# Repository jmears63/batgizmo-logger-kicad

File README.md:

# BatGizmo Logger

This repo contains hardware design files for the BatGizmo Logger PCB, generated in KiCad, including the schematic, PCB layout, and local symbol/footprint libraries for the logger board.

General information can be found in [this blog post](https://twilighttravels.org/2026/04/04/batgizmo-detector-design/). The [firmware can be found here](https://github.com/jmears63/batgizmo-logger-595).

Open the project files in KiCad to see the most recent PCBs.

## What Is the BatGizmo Logger?

The BatGizmo Logger is an ultrasonic microphone that can be used for bat monitoring in two ways:

- Active monitoring, connected via USB to an Android phone or tablet with the [BatGizmo app](https://play.google.com/store/apps/details?id=uk.org.gimell.batgizmoapp) installed.
- Passive monitoring, powered by 3xAA batteries, capable of recording full-spectrum bat data to WAV files stored on an SD card.

## Board Contents

- STM32U5 series microcontroller
- MEMS microphone front end (Infineon IM73A135) with analog conditioning
- microSD connector for local data logging and configuration
- USB Micro-B connector for power and live audio data in active monitoring mode, plus direct firmware update
- Optional real-time clock powered by a CR1220 battery
- On-board mode switch options and status LEDs

## Getting Started

### Prerequisites

- KiCad 8.x (project files are generated with KiCad 8 format)

### Open the Design

1. Launch KiCad.
2. Open `BatGizmo-logger.kicad_pro`.
3. From the project window, open:
   - schematic editor for `BatGizmo-logger.kicad_sch`
   - PCB editor for `BatGizmo-logger.kicad_pcb`

### Regenerate Outputs

Use KiCad's built-in exporters as needed:

- **Schematic Editor** -> ERC, BOM export
- **PCB Editor** -> DRC, Gerbers, drill files, pick-and-place, fabrication docs

Generated fabrication/output artifacts are intentionally ignored in git (see `.gitignore`), so they can be recreated locally per release.

### Build instructions

Detailed build instructions with photographs can be found in the [WIKI](https://github.com/jmears63/batgizmo-logger-kicad/wiki/Building-BatGizmo)

## License

This project is licensed under the **CERN Open Hardware License v2 - Permissive (CERN-OHL-P v2)**.

See `LICENSE.md` for the full text.

Copyright (c) 2024-2026 John Mears.

## Schematic

Open the project files in KiCad to see the most recent schematic.

## Detailed Design Notes
### Capacitors
Decoupling capacitors are provided throughout in accordance with manufacturers' recommendations.

Be aware that surface mount ceramic capacitors generally use high dielectric constant dielectrics to achieve their small size. Unfortunately, the materials used are often piezo electric, meaning that such capacitors act as audio transducers: they can generate sound and act as microphones. Sound and vibrations generated by components are transmitted through the PCB to the MEMS microphone component, which picks it up as sound, thus appearing as narrowband noise in spectrograms. To avoid this, ceramic capacitors must be chosen to have a **class 1 dielectric** such as C0G, or be substituted with tantalum capacitors if appropriate. This is most important for higher value capacitors exposed to widely varying voltages, such as those upstream of power regulators. As a precaution it is wise to use C0G dielectric types for **all** ceramic capacitors.
### Power
The power is derived from either the USB 5V line or the battery holder (if fitted), as selected by the main power switch.
Power is divided into two parts: digital and analogue, with separate LDO regulators to minimize the possibility of digital noise finding its way into the analogue circuitry. The four layer PCB dedicates middle layers to GND and power, divided into separate analogue and digital regions. Analogue power is 3V rather than 3.3V as that is the maximum specified by Infineon for the IM73A135 MEMS microphone. As far as possible, care has been taken to avoid shared 0v return paths between analogue and digital circuitry.

Power related components associated with the MCU are as described in the ST white paper. The MCU variant used includes both internal LDO and SMPS regulators, and can be switched between them under firmware control. SMPS is more efficient in terms of 
power consumption, but may introduce noise. It is therefore only used in auto logger mode where power consumption is important. In other modes the LDO is used. That said, I have seen no difference in noise levels between LDO and SMPS modes. Current consumption is in any case generally low so possibly SMPS mode could be sacrificed, reducing the component count and cost a little.

If the detector is only to be used in active mode (as a USB microphone, not as an unattended logger), the battery holder and power switch need not be fitted, though two pins on latter would need to be connected together on the PCB.

The analogue power LDO can be enabled and disabled by a digital line from the MCU, allowing analogue power to be turned off completely in logger standby mode. Likewise, a high side power switch is used in line with the SD power so that it can also be completely disabled when SD access is not required. Depending on the spec of the SD card actually used, there may or may not be benefit in doing this - another potential simplification opportunity.

### Digital Circuitry
A 16 Mhz crystal is provided for the MCU's "high speed external" clock to provide a stable frequency basis for the data sampling rate. I experimented with using the internal nominally 48 Mhz oscillator for this but it is not stable enough.

A low speed external crystal (32.768 kHz) is provided for the real time clock. Unfortunately, it introduces a faint line at 32.768 kHz in spectrogams because of acoustic coupling through the PCB to the MEMS microphone. This is however at a very low level so not a serious problem. It can be reduced somewhat by pushing a blob of blutack on the crystal to dampen its vibrations.

A CR2012 button battery can be provided to maintain the real time clock when the main batteries are removed. This is a convenience that allows the detector to remember the time and date and avoid the need to reset it frequently. A couple of components could be saved by removing this feature.

A push button is provided as a convenience for firmware update. The MCU enters Direct Firmware Update (DFU) mode when it starts up while the BOOT0 pin is high, allowing firmware to be transferred to and fro over USB. A small cost saving could be achieved by omitting this rarely used button, and instead providing two PCB pads to be shorted with a bent paperclip or similar.

The MCU Master Clock Oscillator (MCO) output is driven from the high speed external clock via PLL1 and a divider, providing a 9.6 Mhz clock. Fine frequency control is possible by using PLL1 fractional part. This allows the data sampling rate to be closely synchonized with the host device's USB frame rate under firmware control, avoiding the issue of handling excess and missing samples. The MCO output is connected with a short trace to Timer 2 external trigger which in turn divides it down to a nominal 384 kHz to trigger the ADC. Different sampling rates are achieved by using different divider ratios.

Serial Wire Debugging (SWD) is provided via a four pin molex connector and associated resistors. These components can be omitted unless firmware development and debugging facilities are required.

An SD card holder and associated decoupling capacitors and pullup resistors provide connectivity to the MCU's SDMMC peripheral, allowing data to be read to and written from an SD card. Writing data to SD requires large and spikey currents from the digital power supply, hence the decoupling capacitors close by. Many SD cards contain internal capacitors with class 2 dielectrics and consequently generate audio that can couple via the PCB to the microphone, ultimately appearing as narrowbound noise sychronized with SD data writes. These are both reasons for placing the SD cardon the opposite corner of the PCB from the sensitive analogue circuitry and microphone. It is worth experimenting with different brands and types of SD card to minimize this issue. If SD card access is not required, for example because only basic active mode is required, these components can be omitted.

Three LEDS (red, amber and green) are driven from three MCU digital IO lines under firmware control. Excessively bright LEDs are annoying in the dark and the series resistors should probably be increased further to reduce dazzle and distraction.

The mode switch has three positions which pull one of three MCU GPIO inputs to ground via a 1k resistor against internal pullup resistors. The auto mode position is also connected to PWR_WKUP2 so the MCU can leave standby if the mode is switched away from auto.

### Analogue Circuitry
Analogue signals are referenced to a mid way voltage reference derived from the analogue power via a passive network and buffered by a low noise op amp. My initial pass at this design used a fancy "low noise" voltage reference chip (MAX6070)for this purpose, but a simple passive network is in fact lower noise and cheaper. You live and learn.

Op amps have been selected with gain-bandwidth products and slew rate limits well in excess of what is required for this circuit, to limit the possibility of signal distortion if limits are approached too closely. The front end op amp that handles the smallest signals is a low noise type, as is the mid way voltage buffer. Testing with a very low distortion sine wave generator at 40 kHz confirms that the analogue path introduces very little distortion, even when operating close to the power rails. The primary source of distortion and noise is actually the MEMS microphone itself, a known limitation of this technology.

The differential signal output from the microphone is amplified by 7.5x and converted to a single ended signal that is filtered by a single pole passive network (~140 kHz). The latter is a nod in the direction of antialias filtering.

That signal provides an input to a programmable gain amplifier (PGA) whose gain is controlled by the MCU under firmware control. The output drives a unity gain buffer and an inverting buffer which provide differential inputs to the MCU ADC. Differential mode reduces common mode noise and results in a better ADC performance according to ST's documentation, confirmed in practice. Those two signals drive the ADC inputs via passive networks including a capacitor very close to the MCU, in line with ST's white paper.

The analogue circuity could be simplified if programmable gain is not required. The differential signals output from the microphone could be directly passed via two op amps to the MCU ADC inputs, preserving differential mode end to end and reducing component count. However, programmable gain is a useful feature.

Higher than standard accuracy components have been used in differential circuitry to maximise the common mode rejection.

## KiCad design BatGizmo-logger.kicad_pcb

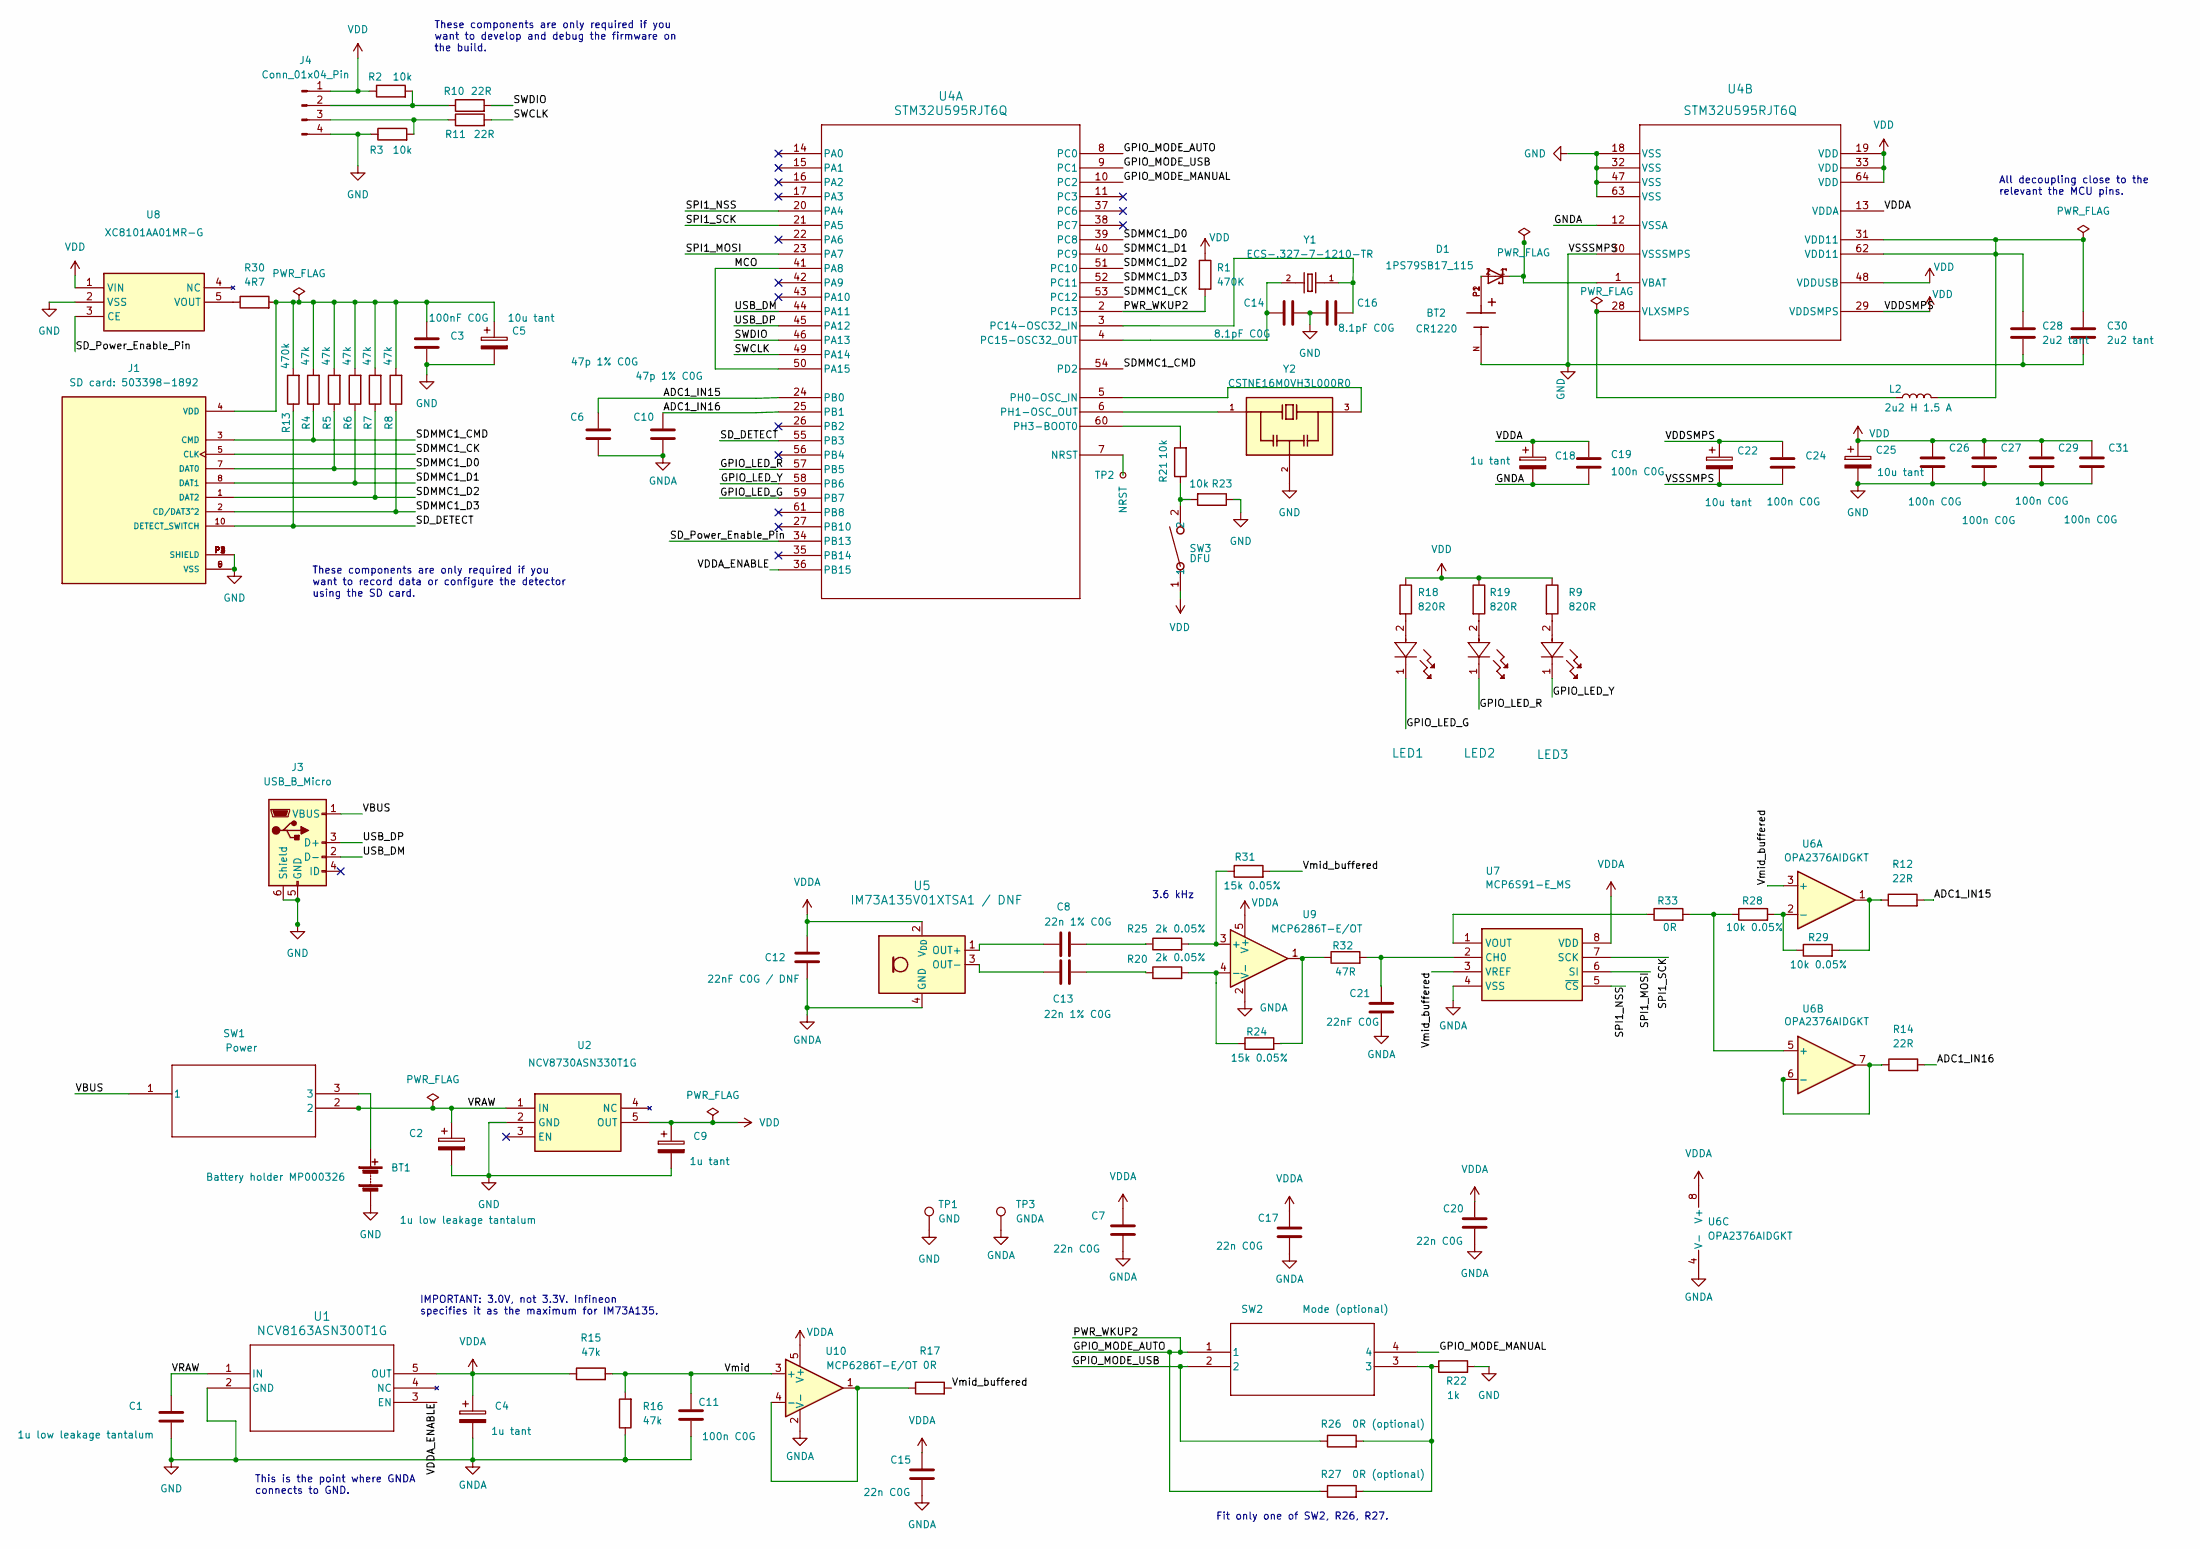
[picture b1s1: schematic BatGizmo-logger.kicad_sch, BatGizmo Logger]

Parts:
BT1: Battery holder MP000326; MP000326 battery holder
BT2: CR1220; BAT_3000; PARTREV M
C1: 1u low leakage tantalum; C_0805_2012Metric_Pad1.18x1.45mm_HandSolder; Farnell Part Number 2773210
C2: 1u low leakage tantalum; CP_EIA-2012-12_Kemet-R; Farnell Part Number 2773210
C3: 100nF C0G; C_1206_3216Metric_Pad1.33x1.80mm_HandSolder
C4, C9, C18: 1u tant; CP_EIA-2012-12_Kemet-R
C5, C22, C25: 10u tant; CP_EIA-2012-12_Kemet-R
C6, C10: 47p 1% C0G; C_0805_2012Metric_Pad1.18x1.45mm_HandSolder
C7, C15, C17, C20: 22n C0G; C_0805_2012Metric_Pad1.18x1.45mm_HandSolder
C8, C13: 22n 1% C0G; C_0805_2012Metric_Pad1.18x1.45mm_HandSolder
C11, C19, C24, C26, C27, C29, C31: 100n C0G; C_1206_3216Metric_Pad1.33x1.80mm_HandSolder
C12: 22nF C0G / DNF; C_0805_2012Metric_Pad1.18x1.45mm_HandSolder
C14, C16: 8.1pF C0G; C_0805_2012Metric_Pad1.18x1.45mm_HandSolder
C21: 22nF C0G; C_0805_2012Metric_Pad1.18x1.45mm_HandSolder
C28, C30: 2u2 tant; C_0805_2012Metric_Pad1.18x1.45mm_HandSolder
D1: 1PS79SB17_115; SOD523
J1: SD card: 503398-1892; MOLEX_503398-1892; PARTREV 0
J3: USB_B_Micro; USB_Micro-B_Molex_47346-0001
J4: Conn_01x04_Pin; PinHeader_1x04_P2.54mm_Vertical
L2: 2u2 H 1.5 A; INDC2016X120N; Manufacturer_Part_Number MURATA 1286AS-H-2R2M=P2; Farnell Part Number 2530046
LED1: 597-6301-607F; LED_1206_3216Metric_ReverseMount
LED2: 597-6001-607F; LED_1206_3216Metric_ReverseMount
LED3: 597-6201-607F; LED_1206_3216Metric_ReverseMount
R1: 470K; R_0805_2012Metric_Pad1.20x1.40mm_HandSolder
R2, R3, R21, R23: 10k; R_0805_2012Metric_Pad1.20x1.40mm_HandSolder
R4, R5, R6, R7, R8, R15, R16: 47k; R_0805_2012Metric_Pad1.20x1.40mm_HandSolder
R9, R18, R19: 820R; R_0805_2012Metric_Pad1.20x1.40mm_HandSolder
R10, R11, R12, R14: 22R; R_0805_2012Metric_Pad1.20x1.40mm_HandSolder
R13: 470k; R_0805_2012Metric_Pad1.20x1.40mm_HandSolder
R17, R33: 0R; R_0805_2012Metric_Pad1.20x1.40mm_HandSolder
R20, R25: 2k 0.05%; R_0805_2012Metric_Pad1.20x1.40mm_HandSolder
R22: 1k; R_0805_2012Metric_Pad1.20x1.40mm_HandSolder
R24, R31: 15k 0.05%; R_0805_2012Metric_Pad1.20x1.40mm_HandSolder
R26, R27: 0R (optional); R_0805_2012Metric_Pad1.20x1.40mm_HandSolder
R28, R29: 10k 0.05%; R_0805_2012Metric_Pad1.20x1.40mm_HandSolder
R30: 4R7; R_0805_2012Metric_Pad1.20x1.40mm_HandSolder
R32: 47R; R_0805_2012Metric_Pad1.20x1.40mm_HandSolder
SW1: Power; SW_SPDT_PCM12; Manufacturer_Part_Number C&K COMPONENTS PCM12SMTR; Farnell Part Number 9575146
SW2: Mode (optional); SW_SP3T_PCM13; Manufacturer_Part_Number C&K COMPONENTS PCM13SMTR; Farnell Part Number 2320077
SW3: DFU; SW_EVQPUJ_4P7X3P5_PAN; Manufacturer_Part_Number PANASONIC EVQPUJ02K; Farnell Part Number 2860923
TP1: GND; TestPoint_Keystone_5019_Minature
TP2: NRST; TestPoint_Pad_1.0x1.0mm
TP3: GNDA; TestPoint_Keystone_5019_Minature
U1: NCV8163ASN300T1G; SOT95P275X110-5N; Farnell Part Number 2981200
U2: NCV8730ASN330T1G; SOT95P275X110-5N; Manufacturer_Part_Number NCV8730ASN330T1G; Mouser Part Number 863-NCV8730ASN330T1G
U4: STM32U595RJT6Q; LQFP64-10x10mm_STM; Farnell Part Number 4228009
U5: IM73A135V01XTSA1 / DNF; Infineon_PG-LLGA-5-2
U6: OPA2376AIDGKT; SOP65P488X118-8N
U7: MCP6S91-E_MS; SOP65P488X118-8N; Manufacturer_Part_Number MCP6S91-E/MS; Mouser Part Number 579-MCP6S91-E/MS
U8: XC8101AA01MR-G; SOT95P280X130-5N; Manufacturer_Part_Number XC8101AA01MR-G; Mouser Part Number 865-XC8101AA01MR-G
U9, U10: MCP6286T-E/OT; SOT-23-5
Y1: ECS-.327-7-1210-TR; XTAL_ECS-.327-7-1210-TR; Farnell Part Number 3649639
Y2: CSTNE16M0VH3L000R0; Resonator_SMD_Murata_CSTxExxV-3Pin_3.0x1.1mm; PARTREV JGC42-8853B; Farnell Part Number 4127639

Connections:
/ADC1_IN15: C6.1, R12.2, U4.24 (PB0)
/ADC1_IN16: C10.1, R14.2, U4.25 (PB1)
/GPIO_LED_G: LED1.1, U4.59 (PB7)
/GPIO_LED_R: LED2.1, U4.57 (PB5)
/GPIO_LED_Y: LED3.1, U4.58 (PB6)
/GPIO_MODE_AUTO: R1.2, R27.1, SW2.1, U4.2 (PC13), U4.8 (PC0)
/GPIO_MODE_MANUAL: SW2.4, U4.10 (PC2)
/GPIO_MODE_USB: R26.1, SW2.2, U4.9 (PC1)
/MCO: U4.41 (PA8), U4.50 (PA15)
/SDMMC1_CK: J1.5 (CLK), U4.53 (PC12)
/SDMMC1_CMD: J1.3 (CMD), R4.1, U4.54 (PD2)
/SDMMC1_D0: J1.7 (DAT0), R5.1, U4.39 (PC8)
/SDMMC1_D1: J1.8 (DAT1), R6.1, U4.40 (PC9)
/SDMMC1_D2: J1.1 (DAT2), R7.1, U4.51 (PC10)
/SDMMC1_D3: J1.2 (CD/DAT3^2), R8.1, U4.52 (PC11)
/SD_DETECT: J1.10 (DETECT_SWITCH), R13.1, U4.55 (PB3)
/SD_Power_Enable_Pin: U4.34 (PB13), U8.3 (CE)
/SPI1_MOSI: U4.23 (PA7), U7.6 (SI)
/SPI1_NSS: U4.20 (PA4), U7.5 (~CS)
/SPI1_SCK: U4.21 (PA5), U7.7 (SCK)
/SWCLK: R11.2, U4.49 (PA14)
/SWDIO: R10.2, U4.46 (PA13)
/USB_DM: J3.2 (D-), U4.44 (PA11)
/USB_DP: J3.3 (D+), U4.45 (PA12)
/VBUS: J3.1 (VBUS), SW1.1
/VDDA_ENABLE: U1.3 (EN), U4.36 (PB15)
/VRAW: C1.1, C2.1, SW1.2, U1.1 (IN), U2.1 (IN)
/Vmid: C11.1, R15.2, R16.2, U10.3 (+)
/Vmid_buffered: R17.2, R31.2, U6.3 (+), U7.3 (VREF)
GND: BT1.2 (-), BT2.N, C1.2, C2.2, C3.2, C4.2, C5.2, C6.2, C7.2, C9.2, C10.2, C11.2, C12.2, C14.2, C15.2, C16.1, C17.2, C18.2, C19.2, C20.2, C21.1, C22.2, C24.2, C25.2, C26.2, C27.2, C28.2, C29.2, C30.2, C31.2, J1.6 (VSS), J1.9 (VSS), J1.P1 (SHIELD), J1.P2 (SHIELD), J1.P3 (SHIELD), J1.P4 (SHIELD), J3.5 (GND), J3.6 (Shield), J4.4, R3.1, R16.1, R22.2, R23.1, TP1.1, TP3.1, U1.2 (GND), U2.2 (GND), U4.12 (VSSA), U4.18 (VSS), U4.30 (VSSSMPS), U4.32 (VSS), U4.47 (VSS), U4.63 (VSS), U5.4 (GND), U5.5 (GND), U6.4 (V-), U7.4 (VSS), U8.2 (VSS), U9.2 (V-), U10.2 (V-), Y2.2
unnamed: BT1.1 (+), SW1.3
unnamed: BT2.P1, BT2.P2, D1.2
unnamed: C8.2, R25.1
unnamed: C13.2, R20.1
unnamed: C28.1, C30.1, L2.2, U4.31 (VDD11), U4.62 (VDD11)
unnamed: C3.1, C5.1, J1.4 (VDD), R4.2, R5.2, R6.2, R7.2, R8.2, R13.2, R30.2
unnamed: J4.2, R2.2, R10.1
unnamed: J4.3, R3.2, R11.1
unnamed: LED1.2, R18.2
unnamed: LED2.2, R19.2
unnamed: LED3.2, R9.2
unnamed: R12.1, R29.2, U6.1
unnamed: R21.1, R23.2, SW3.2
unnamed: R22.1, R26.2, R27.2, SW2.3
unnamed: R24.2, R32.1, U9.1
unnamed: TP2.1, U4.7 (NRST)
unnamed: C16.2, U4.3 (PC14-OSC32_IN), Y1.1
unnamed: C14.1, U4.4 (PC15-OSC32_OUT), Y1.2
unnamed: U4.5 (PH0-OSC_IN), Y2.3
unnamed: U4.6 (PH1-OSC_OUT), Y2.1
unnamed: R21.2, U4.60 (PH3-BOOT0)
unnamed: D1.1, U4.1 (VBAT)
unnamed: L2.1, U4.28 (VLXSMPS)
unnamed: C8.1, U5.1 (OUT+)
unnamed: C13.1, U5.3 (OUT-)
unnamed: R28.2, R29.1, U6.2 (-)
unnamed: R28.1, R33.2, U6.5 (+)
unnamed: R14.1, U6.6 (-), U6.7
unnamed: C21.2, R32.2, U7.2 (CH0)
unnamed: R33.1, U7.1 (VOUT)
unnamed: R30.1, U8.5 (VOUT)
unnamed: R25.2, R31.1, U9.3 (+)
unnamed: R20.2, R24.1, U9.4 (-)
unnamed: R17.1, U10.1, U10.4 (-)
VDD: C9.1, C22.1, C24.1, C25.1, C26.1, C27.1, C29.1, C31.1, J4.1, R1.1, R2.1, R9.1, R18.1, R19.1, SW3.1, U2.5 (OUT), U4.19 (VDD), U4.29 (VDDSMPS), U4.33 (VDD), U4.48 (VDDUSB), U4.64 (VDD), U8.1 (VIN)
VDDA: C4.1, C7.1, C12.1, C15.1, C17.1, C18.1, C19.1, C20.1, R15.1, U1.5 (OUT), U4.13 (VDDA), U5.2 (V_{DD}), U6.8 (V+), U7.8 (VDD), U9.5 (V+), U10.5 (V+)

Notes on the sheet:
These components are only required if you want to develop and debug the firmware on the build.
All decoupling close to the relevant the MCU pins.
Fit only one of SW2, R26, R27.
3.6 kHz
IMPORTANT: 3.0V, not 3.3V. Infineon specifies it as the maximum for IM73A135.
This is the point where GNDA connects to GND.
These components are only required if you want to record data or configure the detector using the SD card.

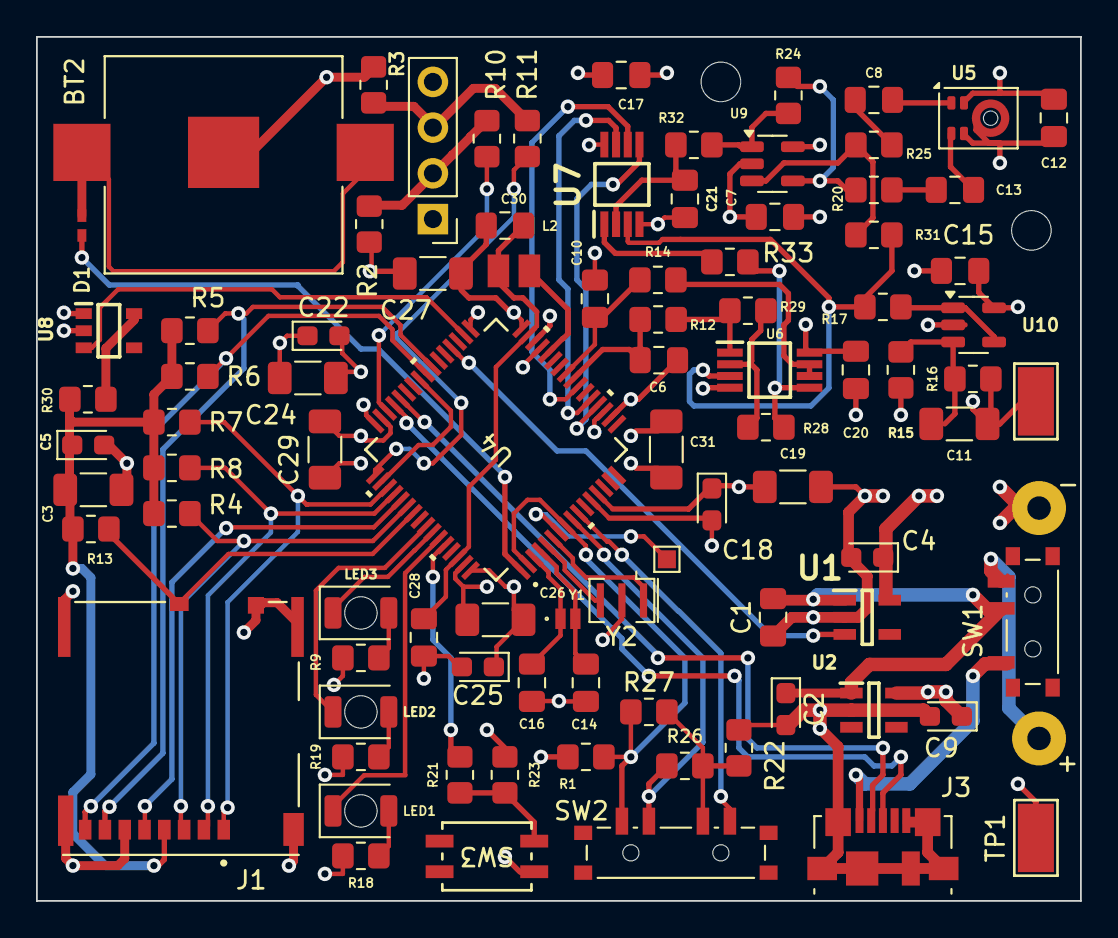
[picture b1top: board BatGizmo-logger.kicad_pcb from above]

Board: 4 copper layers, 58.0 x 48.0 mm, 90 parts (0 on the bottom side), 66 nets.

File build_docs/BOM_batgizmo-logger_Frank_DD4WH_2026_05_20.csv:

ID;Designator;Qty;im Warenkorb;Manufacturer;MfG Part #; Description / Value;Footprint;Type;Note;Anbieter und Referenz
1;R7,R16,R5,R15,R8,R6,R4;7;OK;;47 kohm, ± 1%, 125 mW, 0805 [Metrisch 2012];47 kohm, ± 1%, 125 mW, 0805 [Metrisch 2012];R_0805_2012Metric_Pad1.20x1.40mm_HandSolder;;;
2;C10,C6;2;OK;Vishay;VJ0805A470GXXCW1BC;47p  1% C0G;C_0805_2012Metric_Pad1.18x1.45mm_HandSolder;;;Mouser 77-VJ0805A470GXXCBC
3;SW3;1;OK;Panasonic;EVQ-PUJ02K;DFU;SW_EVQPUJ_4P7X3P5_PAN;;;
4;C19,C29,C26,C11,C27,C31,C24;7;OK, vorhanden;;;100n C0G;C_1206_3216Metric_Pad1.33x1.80mm_HandSolder;;;
5;J1;1;OK;Molex;5033981892;503398-1892;MOLEX_503398-1892;;;Digikey WM11190CT-ND
6;U6;1;OK;Texas Instruments;OPA2376AIDGKT;OPA2376AIDGKT;SOP65P488X118-8N;;;Mouser 595-OPA2376AIDGKT
7;C22,C5,C25;3;OK;Kyocera AVX;F921A106MPA;10u tant;CP_EIA-2012-12_Kemet-R;;;Digikey 478-11412-1-ND
8;C17,C7,C15,C20;4;OK;Murata;GCM21B5C1H223FA16L;22n  1% C0G;C_0805_2012Metric_Pad1.18x1.45mm_HandSolder;;;Mouser 81-GCM21B5C1H223FA6L
9;R21,R2,R23,R3;4;OK;;10 kohm, ± 1%, 125 mW, 0805 [Metrisch 2012];10 kohm, ± 1%, 125 mW, 0805 [Metrisch 2012];R_0805_2012Metric_Pad1.20x1.40mm_HandSolder;;;
10;C14,C16;2;OK;Kyocera;08053A2R0CAT2A;2p C0G;C_0805_2012Metric_Pad1.18x1.45mm_HandSolder;;;Mouser 77-VJ0805A470GXXCBC
11;BT1;1;OK;;;Battery holder MP000326;MP000326 battery holder;;;Farnell 3126562
12;Y1;1;OK;ECS;ECS-.327-7-1210-TR;ECS-.327-7-1210-TR;XTAL_ECS-.327-7-1210-TR;;;
13;Y2;1;OK;Murata;CSTNE16M0VH3L000R0;CSTNE16M0VH3L000R0;Resonator_SMD_Murata_CSTxExxV-3Pin_3.0x1.1mm;;;
14;TP2;1;;;;NRST;TestPoint_Pad_1.0x1.0mm;;;
15;R12,R10,R14,R11;4;OK;;22 ohm, ± 5%, 250 mW, 0805 [Metrisch 2012];22 ohm, ± 5%, 250 mW, 0805 [Metrisch 2012];R_0805_2012Metric_Pad1.20x1.40mm_HandSolder;;;
16;LED2;1;OK;Dialight;597-6001-607F;597-6001-607F RED;LED_1206_3216Metric_ReverseMount;;;Farnell 3548406
17;LED1;1;OK;Dialight;597-6001-607F;597-6301-607F;LED_1206_3216Metric_ReverseMount;;;Farnell 3548407
18;C1;1;OK;Vishay Sprague;TMCP1E105MTRF;1u low leakage tantalum;C_0805_2012Metric_Pad1.18x1.45mm_HandSolder;;;Digikey 718-2506-1-ND
19;R13;1;OK;;;470k;R_0805_2012Metric_Pad1.20x1.40mm_HandSolder;;;Digikey CR0805-FX-4703ELFCT-ND
20;R26,R27;2;OK;;;0R (optional);R_0805_2012Metric_Pad1.20x1.40mm_HandSolder;;;Digikey 541-4125-1-ND
21;J4;1;OK, vorhanden;;;Conn_01x04_Pin;PinHeader_1x04_P2.54mm_Vertical;;;
22;SW1;1;OK;C&K;PCM12SMTR;Power;SW_SPDT_PCM12;;;Digikey 401-2016-1-ND
23;U2;1;OK;onsemi;NCV8730ASN330T1G;NCV8730ASN330T1G;SOT95P275X110-5N;;;Digikey 488-NCV8730ASN330T1GCT-ND
24;R32;1;OK;;47 ohm, ± 5%, 500 mW, 0805 [Metrisch 2012];47 ohm, ± 5%, 500 mW, 0805 [Metrisch 2012];R_0805_2012Metric_Pad1.20x1.40mm_HandSolder;;;Farnell 3646422
25;R31,R24;2;OK;;15 kohm, ± 0.05%, 0805 [Metrisch 2012];15 kohm, ± 0.05%, 0805 [Metrisch 2012];R_0805_2012Metric_Pad1.20x1.40mm_HandSolder;;;Digikey P15KBSCT-ND
26;LED3;1;OK;Dialight;597-6201-607F;597-6201-607F Orange;LED_1206_3216Metric_ReverseMount;;;Farnell 4256558
27;C30,C28;2;OK;Vishay Sprague;TMCP1A225MTRF;2u2 tant;C_0805_2012Metric_Pad1.18x1.45mm_HandSolder;;;Digikey 718-2492-1-ND
28;TP1;1;;;;GND;TestPoint_Keystone_5019_Minature;;;
29;R1;1;OK;;;470K;R_0805_2012Metric_Pad1.20x1.40mm_HandSolder;;;
30;R33,R17;2;OK;;;0R;R_0805_2012Metric_Pad1.20x1.40mm_HandSolder;;;
31;C3;1;OK, vorhanden;;;100nF C0G;C_1206_3216Metric_Pad1.33x1.80mm_HandSolder;;;
32;R19,R18,R9;3;OK;;820 ohm, ± 5%, 500 mW, 0805 [Metrisch 2012];820 ohm, ± 5%, 500 mW, 0805 [Metrisch 2012];R_0805_2012Metric_Pad1.20x1.40mm_HandSolder;;;Farnell 3646456
33;U5;1;OK;Infineon;IM73A135V01XTSA1;IM73A135V01XTSA1 / DNF;Infineon_PG-LLGA-5-2;;;Digikey 448-IM73A135V01XTSA1CT-ND
34;SW2;1;OK;Littelfuse;PCM13SMTR;Mode (optional);SW_SP3T_PCM13;;;
35;C4,C18,C9;3;OK;Vishay Sprague;TMCP1E105MTRF;1u tant;CP_EIA-2012-12_Kemet-R;;;Digikey 718-2506-1-ND
36;U8;1;OK;Torex;XC8101AA01MR-G;XC8101AA01MR-G;SOT95P280X130-5N;;;Farnell 3535604
37;TP3;1;;;;GNDA;TestPoint_Keystone_5019_Minature;;;
38;U1;1;OK;onsemi;NCV8163ASN300T1G;NCV8163ASN300T1G 3.0 Volts;SOT95P275X110-5N;;;Digikey 488-NCV8163ASN300T1GCT-ND
39;U4;1;OK;STMicroelectronics;STM32U595RJT6Q;STM32U595RIT6;LQFP64-10x10mm_STM;;;Mouser 511-STM32U595RJT6Q 
40;U10,U9;2;OK;Microchip;MCP6286T-E/OT;MCP6286T-E/OT;SOT-23-5;;;Farnell 1825038
41;R22;1;OK;;;1k;R_0805_2012Metric_Pad1.20x1.40mm_HandSolder;;;Digikey 311-1.00KCRCT-ND
42;R29,R28;2;OK;;10k 0.05%;10k 0.05%;R_0805_2012Metric_Pad1.20x1.40mm_HandSolder;;;Digikey RG20N10.0KWCT-ND
43;C2;1;OK;Vishay Sprague;TMCP1E105MTRF;1u low leakage tantalum;CP_EIA-2012-12_Kemet-R;;;Digikey 718-2506-1-ND
44;J3;1;OK;Molex;47346-0001;USB_B_Micro;USB_Micro-B_Molex_47346-0001;;;Farnell 1568026
45;C21;1;OK;Murata;GCM21B5C1H223FA16L;22n  1% C0G;C_0805_2012Metric_Pad1.18x1.45mm_HandSolder;;;Mouser 81-GCM21B5C1H223FA6L
46;L2;1;OK;Murata;1286AS-H-2R2M=P2;2u2 H 1.5 A;INDC2016X120N;;;Farnell 2530046
47;BT2;1;OK;Keystone Electronics;3000;CR1220;BAT_3000;;;Digikey 36-3000-ND
48;D1;1;OK;onsemi;RB521S30T1G;1PS79SB17_115;SOD523;;;
49;R20,R25;2;OK;;2 kohm, ± 0.05%, 125 mW, 0805 [Metrisch 2012];2 kohm, ± 0.05%, 125 mW, 0805 [Metrisch 2012];R_0805_2012Metric_Pad1.20x1.40mm_HandSolder;;;Farnell 2797332
50;C8,C13;2;OK;Murata;GCM21B5C1H223FA16L;22n  1% C0G;C_0805_2012Metric_Pad1.18x1.45mm_HandSolder;;;Mouser 81-GCM21B5C1H223FA6L
51;C12;1;OK;Murata;GCM21B5C1H223FA16L;22nF C0G / DNF;C_0805_2012Metric_Pad1.18x1.45mm_HandSolder;;;Mouser 81-GCM21B5C1H223FA6L
52;U7;1;OK;Mikrochip;MCP6S91-E/MS;MCP6S91-E_MS;SOP65P488X118-8N;;;Digikey MCP6S91-E/MS-ND
53;R30;1;OK;;4R7;4R7;R_0805_2012Metric_Pad1.20x1.40mm_HandSolder;;;Digikey 13-RT0805FRE074R7LCT-ND

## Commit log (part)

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2026-03-31 Initial commit.
2026-03-31 Added all project files with copyright and licence.
2026-03-31 Updated README.md, including images of the PCB.
2026-03-31 Updates to README.md.
2026-03-31 Added an image of the schematic.
2026-04-04 Added detailed design notes to README.md.
2026-04-04 Added some links to README.md.
2026-05-30 Added source code and .stl files for exponential horns to use with this PCB.
2026-06-22 Minor tidy up in readme text.
2026-06-22 Fixed more typos in README.txt.

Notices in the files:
BatGizmo-logger.kicad_pcb:
(c) Copyright 2023-2025 John Mears
BatGizmo-logger.kicad_sch:
This source describes Open Hardware and is licensed under the
CERN-OHL-P v2.
